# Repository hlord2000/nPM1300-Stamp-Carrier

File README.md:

# nPM1300 Stamp Carrier Board

## Overview

Companion carrier board for the nPM1300 Stamp, providing additional functionality and connectivity options. Designed for rapid prototyping and development with the nPM1300 PMIC.

## Key Features

- USB-C port for power
- ESD protection
- Ship mode button
- User button on GPIO0
- Two STEMMA QT ports
- Pin headers for all nPM1300 Stamp connections
- RGB LED
- JST-PH and JST-SH battery connectors
- Configurable solder jumpers

## Design Resources

- Schematic available
- PCB design files available

## Solder Jumper Options

- VDDIO source selection
- NTC thermistor bypass
- Load switch to LDO conversion

## Usage Notes

- Compatible with nPM1300 Stamp
- Provides all external components required by nPM1300
- I2C pull-ups included
- ESD protection provided for USB-C and battery connections

For detailed specifications of the nPM1300, visit [Nordic Semiconductor's nPM1300 page](https://www.nordicsemi.com/Products/nPM1300).

For information about the nPM1300 Stamp, see the [nPM1300 Stamp Repository](https://github.com/hlord2000/nPM1300-Stamp).

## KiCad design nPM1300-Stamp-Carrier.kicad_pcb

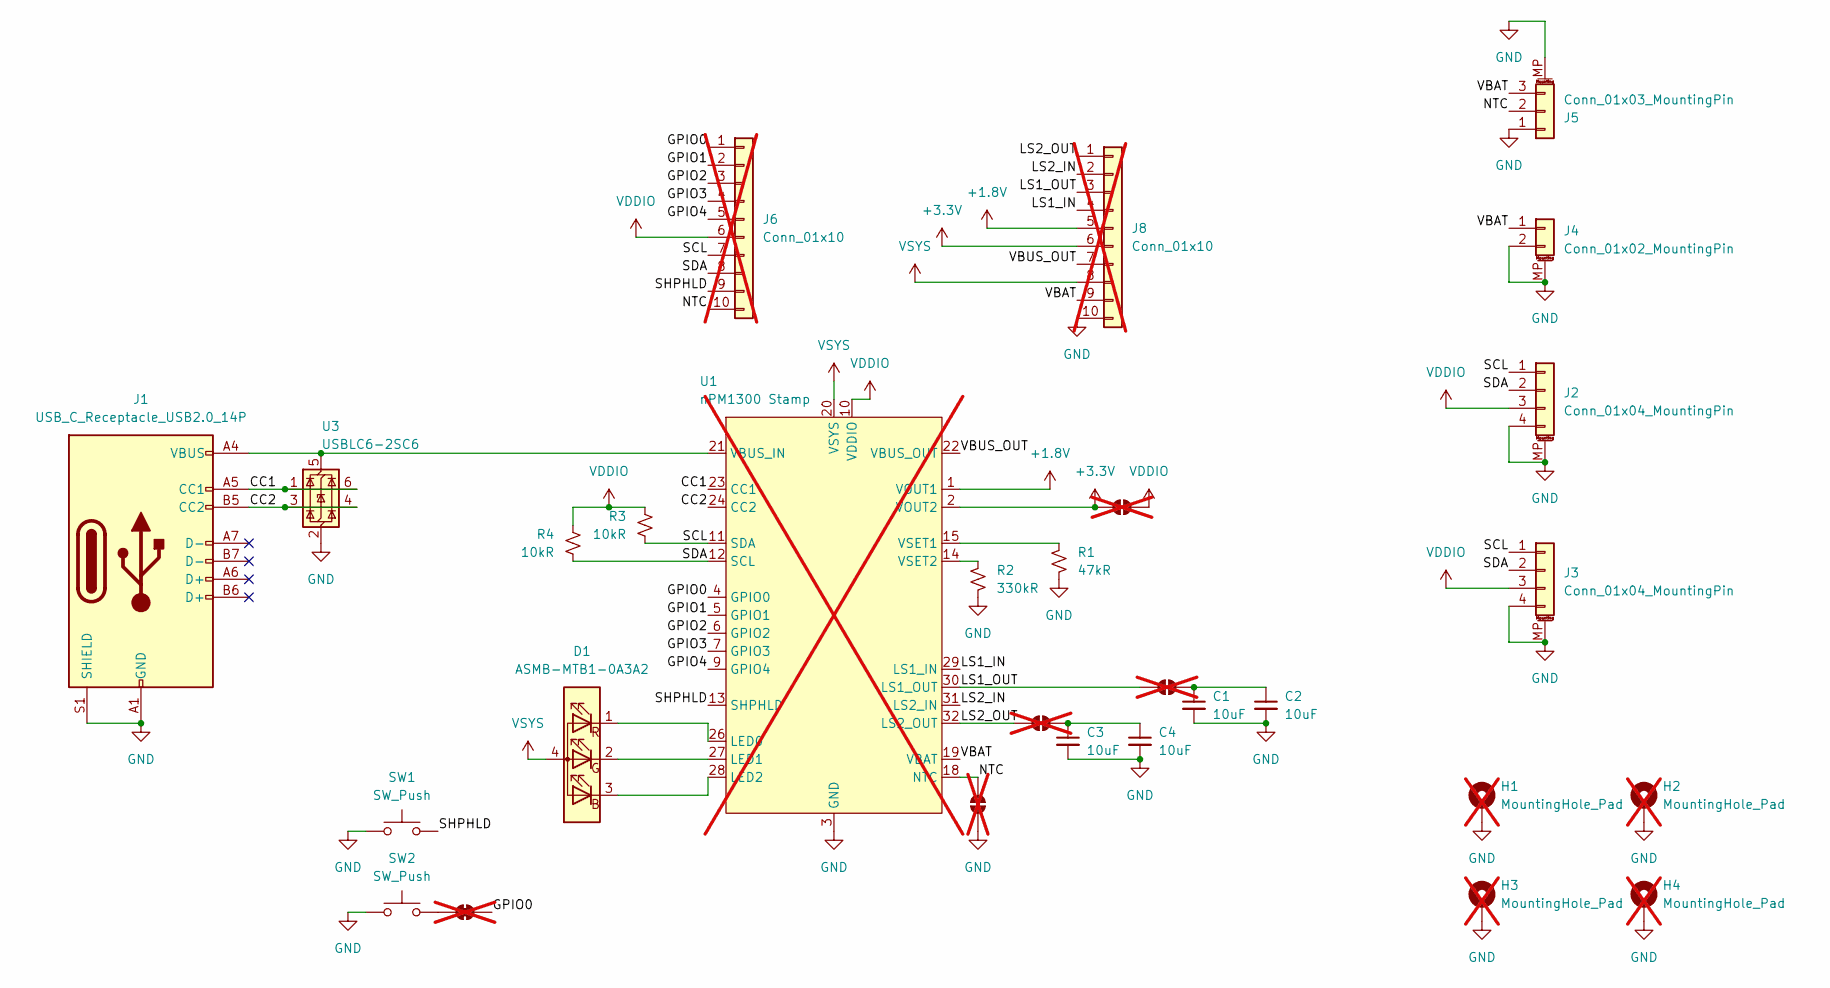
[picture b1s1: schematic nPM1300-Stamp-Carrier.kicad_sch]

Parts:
C1, C2, C3, C4: 10uF; C_0603_1608Metric; LCSC C96446
D1: ASMB-MTB1-0A3A2; LED_Avago_PLCC4_3.2x2.8mm_CW; LCSC C516144
H1, H2, H3, H4: MountingHole_Pad; MountingHole_2.5mm_Pad_TopBottom; not fitted
J1: USB_C_Receptacle_USB2.0_14P; USB_C_Receptacle_HRO_TYPE-C-31-M-12; LCSC C2765186
J2, J3: Conn_01x04_MountingPin; JST_SH_SM04B-SRSS-TB_1x04-1MP_P1.00mm_Horizontal; LCSC C7433425
J4: Conn_01x02_MountingPin; JST_PH_S2B-PH-SM4-TB_1x02-1MP_P2.00mm_Horizontal; LCSC C3029440
J5: Conn_01x03_MountingPin; JST_SH_SM03B-SRSS-TB_1x03-1MP_P1.00mm_Horizontal; LCSC C7433424
J6, J8: Conn_01x10; PinHeader_1x10_P2.54mm_Vertical; not fitted
JP1, JP2, JP3, JP4: SolderJumper_2_Open; SolderJumper-2_P1.3mm_Open_Pad1.0x1.5mm; not fitted
JP5: SolderJumper_2_Bridged; SolderJumper-2_P1.3mm_Bridged_Pad1.0x1.5mm; not fitted
R1: 47kR; R_0402_1005Metric; LCSC C25792
R2: 330kR; R_0402_1005Metric; LCSC C25778
R3, R4: 10kR; R_0402_1005Metric; LCSC C25744
SW1, SW2: SW_Push; SW_Push_1P1T_NO_Vertical_Wuerth_434133025816; LCSC C139797
U1: nPM1300 Stamp; nPM1300-Stamp_18x18_Pitch2mm; not fitted
U3: USBLC6-2SC6; SOT-23-6; LCSC C5180249

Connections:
+1.8V: J8.5, U1.1 (VOUT1)
+3.3V: J8.6, JP4.2 (B), U1.2 (VOUT2)
/CC1: J1.A5 (CC1), U1.23 (CC1), U3.1 (I/O1), U3.6 (I/O1)
/CC2: J1.B5 (CC2), U1.24 (CC2), U3.3 (I/O2), U3.4 (I/O2)
/GPIO0: J6.1, JP5.2 (B), U1.4 (GPIO0)
/GPIO1: J6.2, U1.5 (GPIO1)
/GPIO2: J6.3, U1.6 (GPIO2)
/GPIO3: J6.4, U1.7 (GPIO3)
/GPIO4: J6.5, U1.9 (GPIO4)
/LS1_IN: J8.4, U1.29 (LS1_IN)
/LS1_OUT: J8.3, JP1.2 (B), U1.30 (LS1_OUT)
/LS2_IN: J8.2, U1.31 (LS2_IN)
/LS2_OUT: J8.1, JP2.2 (B), U1.32 (LS2_OUT)
/NTC: J5.2, J6.10, JP3.1 (A), U1.18 (NTC)
/SCL: J2.1, J3.1, J6.7, R3.2, U1.11 (SDA)
/SDA: J2.2, J3.2, J6.8, R4.2, U1.12 (SCL)
/SHPHLD: J6.9, SW1.2, U1.13 (SHPHLD)
/VBAT: J4.1, J5.3, J8.9, U1.19 (VBAT)
/VBUS_OUT: J8.7, U1.22 (VBUS_OUT)
GND: C1.2, C2.2, C3.2, C4.2, H1.1, H2.1, H3.1, H4.1, J1.A1 (GND), J1.A12 (GND), J1.B1 (GND), J1.B12 (GND), J1.S1 (SHIELD), J2.4, J2.MP (MountPin), J3.4, J3.MP (MountPin), J4.2, J4.MP (MountPin), J5.1, J5.MP (MountPin), J8.10, JP3.2 (B), R1.2, R2.2, SW1.1, SW2.1, U1.3 (GND), U1.8 (GND), U1.16 (GND), U1.17 (GND), U1.25 (GND), U3.2 (GND)
unnamed: D1.3 (BK), U1.28 (LED2)
unnamed: D1.2 (GK), U1.27 (LED1)
unnamed: D1.1 (RK), U1.26 (LED0)
unnamed: C1.1, C2.1, JP1.1 (A)
unnamed: C3.1, C4.1, JP2.1 (A)
unnamed: JP5.1 (A), SW2.2
unnamed: J1.A4 (VBUS), J1.A9 (VBUS), J1.B4 (VBUS), J1.B9 (VBUS), U1.21 (VBUS_IN), U3.5 (VBUS)
unnamed: R1.1, U1.15 (VSET1)
unnamed: R2.1, U1.14 (VSET2)
VDDIO: J2.3, J3.3, J6.6, JP4.1 (A), R3.1, R4.1, U1.10 (VDDIO)
VSYS: D1.4 (A), J8.8, U1.20 (VSYS)

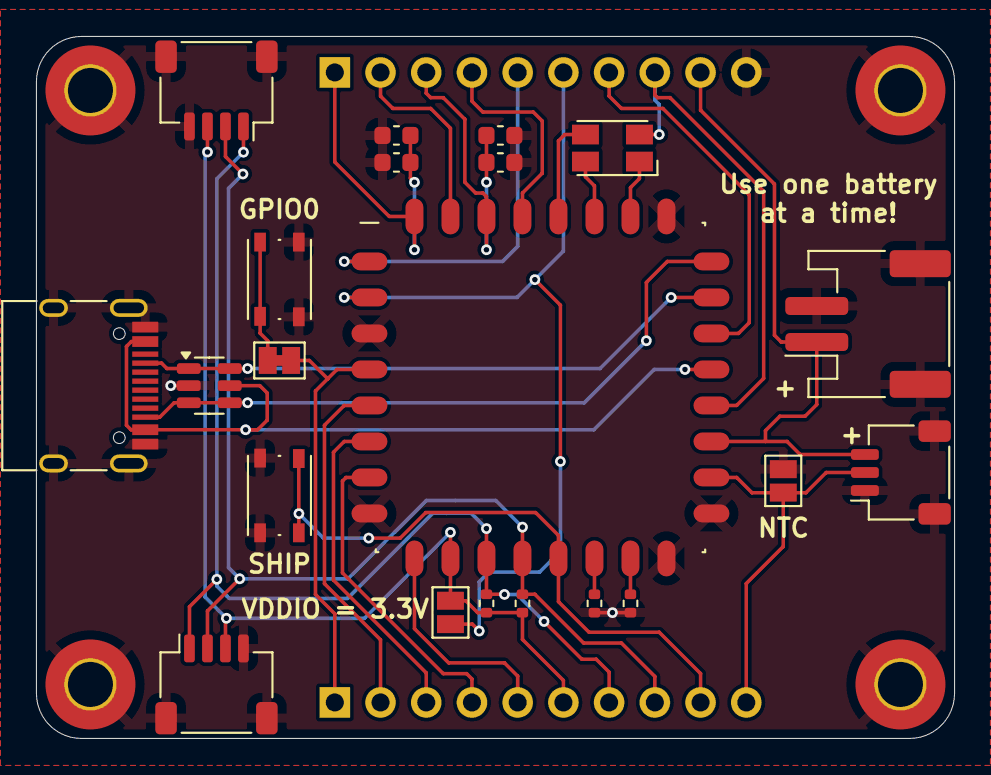
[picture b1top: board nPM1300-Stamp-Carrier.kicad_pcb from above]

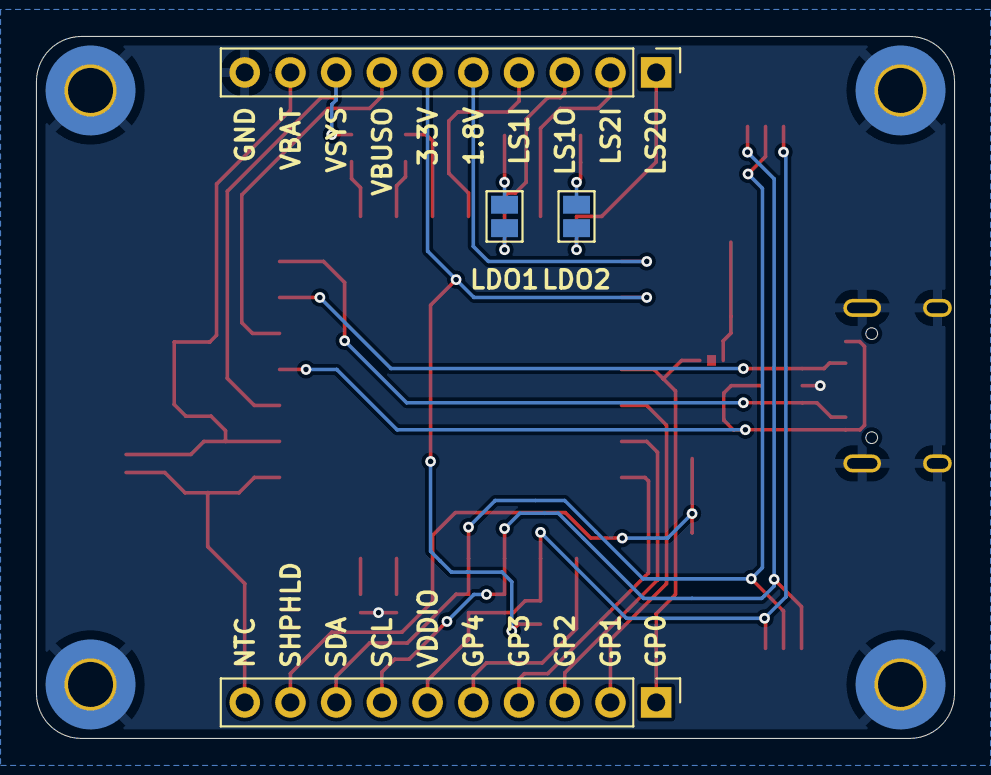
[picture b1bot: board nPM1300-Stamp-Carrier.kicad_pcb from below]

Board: 2 copper layers, 51.0 x 39.0 mm, 29 parts (4 on the bottom side), 31 nets.

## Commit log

2024-10-02 Initial commit.
2024-10-02 Small README change mentioning lack of USB data out
